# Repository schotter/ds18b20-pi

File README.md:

<div style="font-size: 48pt; color: #e33;">DO NOT USE!</div>

Never produced and it's constructed in a stupid way.
It ignores 1-Wire's bus structure.

<hr/>

# ds18b20-pi

A simple extension board for the raspberry pi 1 model **b** with only **26** GPIO pins.
It's purpose is to make GPIO**4** easily accessible, because it's used for the [1-Wire](https://en.wikipedia.org/wiki/1-Wire) bus.
By easily I mean by using [screw terminal](https://www.reichelt.de/leiterplattenklemme-3-polig-rm-3-5-mm-dg350-3-5-3-p276225.html?&nbc=1)s.
As the [1-Wire](https://en.wikipedia.org/wiki/1-Wire) bus is a **bus**, it makes no sense to create several junctions on the pcb.
Just turn the cable into a [cable harness](https://en.wikipedia.org/wiki/Cable_harness).

That "trick" created space which is now used to switch a floor heating's automatic control electric motor.
Those motors are pretty dumb.
If powered the motor opens the valve, if not it closes the valve.
So there is no communication protocol, just a simple "on/off switch" that can be implemented by a GPIO pin, a relay, a [free-wheeling diode](https://en.wikipedia.org/wiki/Flyback_diode) and a [mosfet](https://en.wikipedia.org/wiki/MOSFET) because the relay needs 5V.
Normally I would add a pull-down resistor (10k) to every mosfet's gate, but there is not enough space.
If things get messy it should be possible to place tht resistors at the bottom side or maybe even just smd resistors between every mosfet's source (square) and gate (middle) pin.

The green leds were added to signal the relay's status and are kind of optional.
As the wires to all sensors got pretty long a [tvs-diode](https://en.wikipedia.org/wiki/Transient-voltage-suppression_diode) was added to prevent damage from esd events.
Unfortunately there is no tht version so I had to pick a smd package.

## bom

| part | description | price | manufacturer | datasheet |
|------|-------------|-------|--------------|-----------|
| [2N 7000 DIO](https://www.reichelt.de/mosfet-n-ch-60v-0-115a-0-4w-to-92-2n-7000-dio-p219075.html) | n-channel mosfet | 0,08 € | [diotec](https://diotec.com/en/productlist.html?productfamily=FET) | [pdf](https://diotec.com/tl_files/diotec/files/pdf/datasheets/2n7000.pdf) |
| [BAT 48 STM](https://www.reichelt.de/schottkydiode-40-v-0-35-a-do-35-bat-48-stm-p219563.html) | schottky diode | 0,04 € | [st](https://www.st.com/en/diodes-and-rectifiers/bat48.html) | [pdf](https://www.st.com/resource/en/datasheet/bat48.pdf) |
| [DG350 3,5-2](https://www.reichelt.de/leiterplattenklemme-2-polig-rm-3-5-mm-dg350-3-5-2-p276224.html) | connector 2-pins | 0,19 € | [degson](http://degson.de/en/pro_detail/id/542) | [pdf](http://degson.de/en/downpdf/id/542.html) |
| [DG350 3,5-3](https://www.reichelt.de/leiterplattenklemme-3-polig-rm-3-5-mm-dg350-3-5-3-p276225.html) | connector 3-pins | 0,28 € | [degson](http://degson.de/en/pro_detail/id/542) | [pdf](http://degson.de/en/downpdf/id/542.html) |
| [HJR-4102-L 5V](https://www.reichelt.de/dil-miniaturrelais-hjr-4102-5v-1-wechsler-5a-hjr-4102-l-5v-p101950.html) | relay | 0,62 € | [tianbo](http://www.tianbo-relay.com/en/products.php?tid=10) | [pdf](http://www.tianbo-relay.com/upload/2019062414532076.pdf) |
| [K-O RD12JN152T52](https://www.reichelt.de/widerstand-kohleschicht-1-5-kohm-0411-500-mw-5-k-o-rd12jn152t52-p237423.html) | 1,5k resistor | 0,08 € | | |
| [LED 3MM 5V GN](https://www.reichelt.de/led-3-mm-bedrahtet-5-v-gruen-20-mcd-60-led-3mm-5v-gn-p54093.html) | green led with embedded resistor | 0,31 € | [kingbright](https://www.kingbright.com/content/listitem/psearch/259) | [pdf](https://cdn-reichelt.de/documents/datenblatt/A500/L-934GD-5V.pdf) |
| [PESD3V3S2UT](https://www.reichelt.de/doppe-esd-schutzdiode-3-3-vrwm-20-vcl-30kv-sot-23-pesd3v3s2ut-p271905.html) | TVS-diode | 0,12 € | [nxp](https://www.nexperia.com/products/esd-protection-tvs-filtering-and-signal-conditioning/automotive-esd-protection-and-tvs/automotive-esd-protection/PESD3V3S2UT.html) | [pdf](https://assets.nexperia.com/documents/data-sheet/PESDXS2UT_SERIES.pdf) |

## schematic

## board

## rendering 

Raspberry Pi 1 GPIO extension board for the 1-wire bus

## note

* `pcb_new`: `File -> Export -> SVG`, *all layers in a single file*, *print board edges*, *color*
* `eeschema`: `File -> Plot`, *SVG*, *Page Size: A4*, *Output mode: color*, *Plot border and title block*

```
$ convert -background white schematic_export.svg schematic_export.png
$ convert -background none board_export.svg board_export.png
```

`convert` is part of [ImageMagick](https://imagemagick.org/index.php).

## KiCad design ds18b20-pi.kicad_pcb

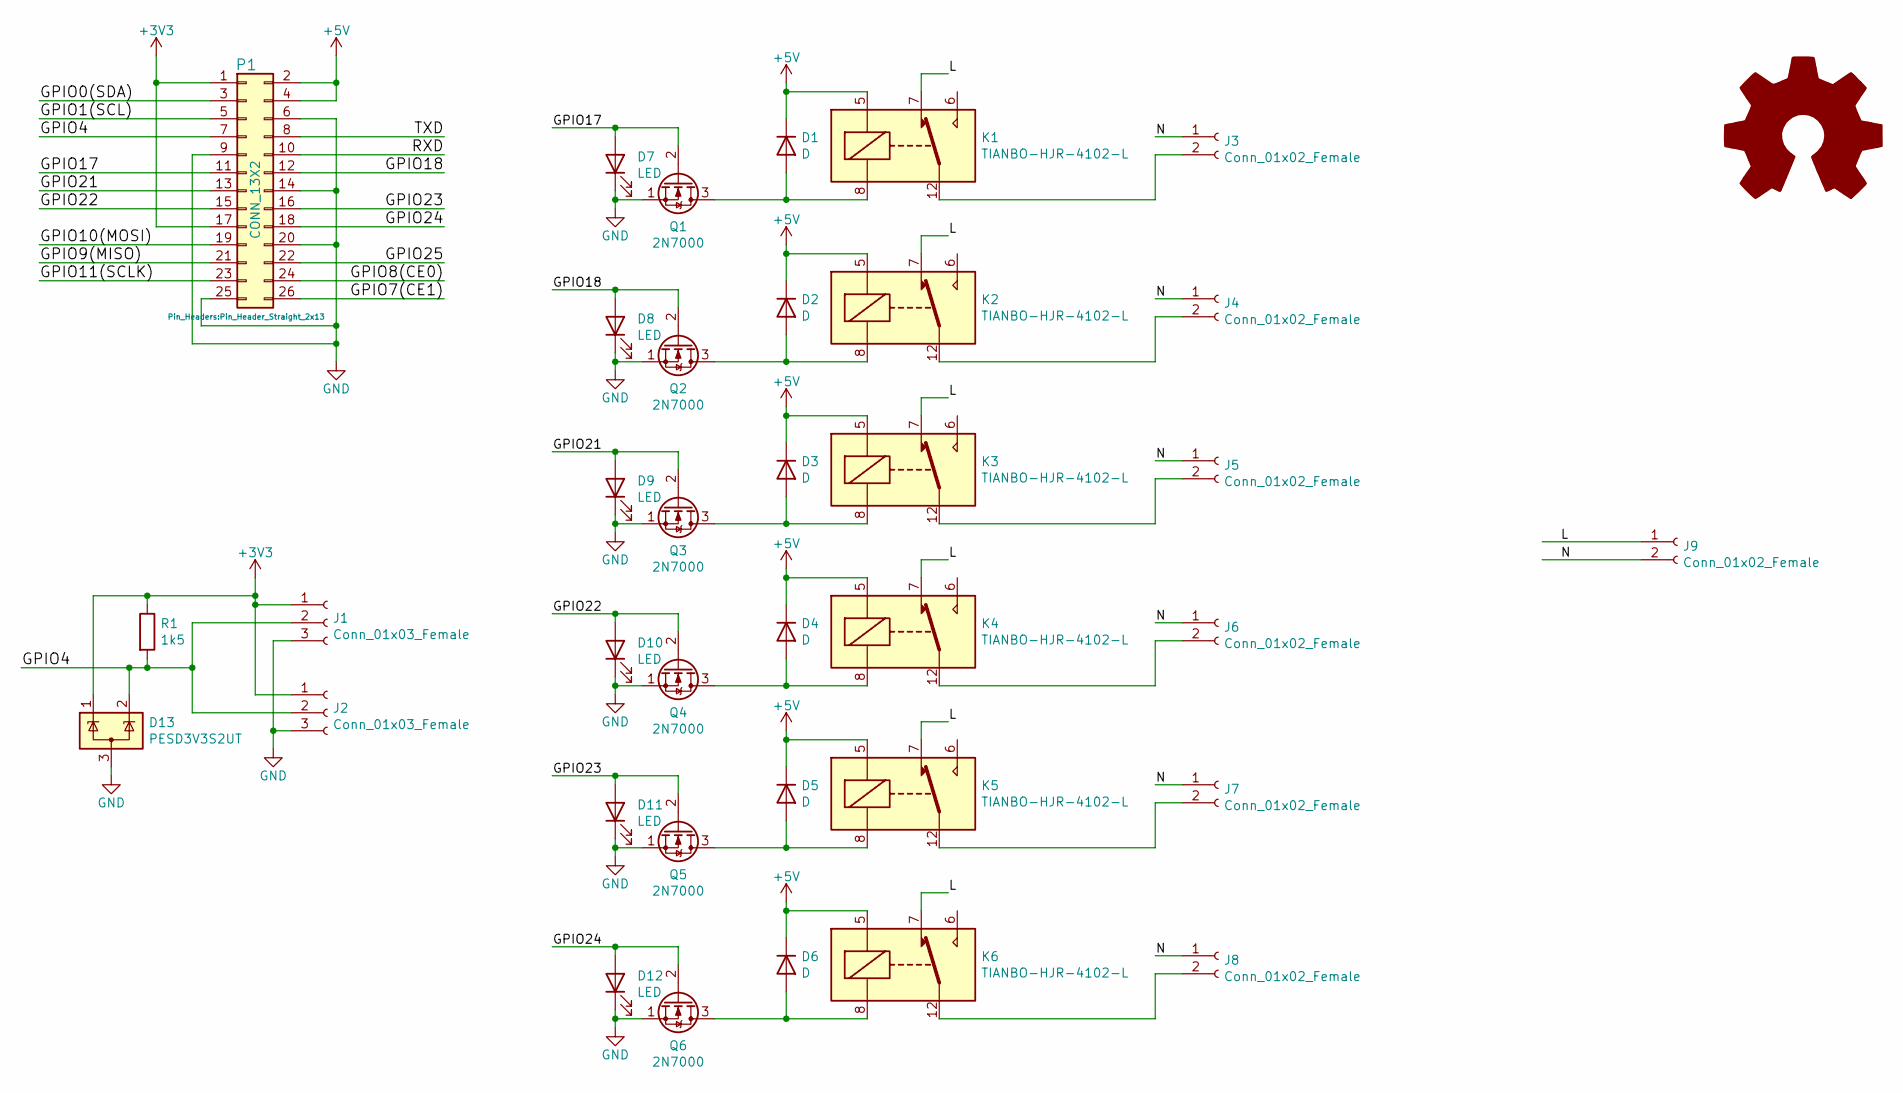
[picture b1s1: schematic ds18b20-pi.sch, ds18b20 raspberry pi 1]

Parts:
D1, D2, D3, D4, D5, D6: D; D_DO-35_SOD27_P7.62mm_Horizontal
D7, D8, D9, D10, D11, D12: LED; LED_D3.0mm
D13: PESD3V3S2UT; SOT-23
J1, J2: Conn_01x03_Female; PhoenixContact_MC_1,5_3-G-3.5_1x03_P3.50mm_Horizontal
J3, J4, J5, J6, J7, J8, J9: Conn_01x02_Female; PhoenixContact_MC_1,5_2-G-3.5_1x02_P3.50mm_Horizontal
K1, K2, K3, K4, K5, K6: TIANBO-HJR-4102-L; Relay_SPDT_HJR-4102
P1: CONN_13X2; Pin_Header_Straight_2x13
Q1, Q2, Q3, Q4, Q5, Q6: 2N7000; TO-92_Inline
R1: 1k5; R_Axial_DIN0411_L9.9mm_D3.6mm_P12.70mm_Horizontal

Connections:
+3V3: D13.1 (K), J1.1, J2.1, P1.1, P1.17, R1.1
+5V: D1.1 (K), D2.1 (K), D3.1 (K), D4.1 (K), D5.1 (K), D6.1 (K), K1.5, K2.5, K3.5, K4.5, K5.5, K6.5, P1.2, P1.4
/GPIO0(SDA): P1.3
/GPIO1(SCL): P1.5
/GPIO4: D13.2 (K), J1.2, J2.2, P1.7, R1.2
/GPIO7(CE1): P1.26
/GPIO8(CE0): P1.24
/GPIO9(MISO): P1.21
/GPIO10(MOSI): P1.19
/GPIO11(SCLK): P1.23
/GPIO17: D7.2 (A), P1.11, Q1.2 (G)
/GPIO18: D8.2 (A), P1.12, Q2.2 (G)
/GPIO21: D9.2 (A), P1.13, Q3.2 (G)
/GPIO22: D10.2 (A), P1.15, Q4.2 (G)
/GPIO23: D11.2 (A), P1.16, Q5.2 (G)
/GPIO24: D12.2 (A), P1.18, Q6.2 (G)
/GPIO25: P1.22
/L: J9.1, K1.7, K2.7, K3.7, K4.7, K5.7, K6.7
/N: J3.1, J4.1, J5.1, J6.1, J7.1, J8.1, J9.2
/RXD: P1.10
/TXD: P1.8
GND: D7.1 (K), D8.1 (K), D9.1 (K), D10.1 (K), D11.1 (K), D12.1 (K), D13.3 (A), J1.3, J2.3, P1.6, P1.9, P1.14, P1.20, P1.25, Q1.1 (S), Q2.1 (S), Q3.1 (S), Q4.1 (S), Q5.1 (S), Q6.1 (S)
unnamed: D1.2 (A), K1.8, Q1.3 (D)
unnamed: D2.2 (A), K2.8, Q2.3 (D)
unnamed: D3.2 (A), K3.8, Q3.3 (D)
unnamed: D4.2 (A), K4.8, Q4.3 (D)
unnamed: D5.2 (A), K5.8, Q5.3 (D)
unnamed: D6.2 (A), K6.8, Q6.3 (D)
unnamed: J3.2, K1.12
unnamed: J4.2, K2.12
unnamed: J5.2, K3.12
unnamed: J6.2, K4.12
unnamed: J7.2, K5.12
unnamed: J8.2, K6.12

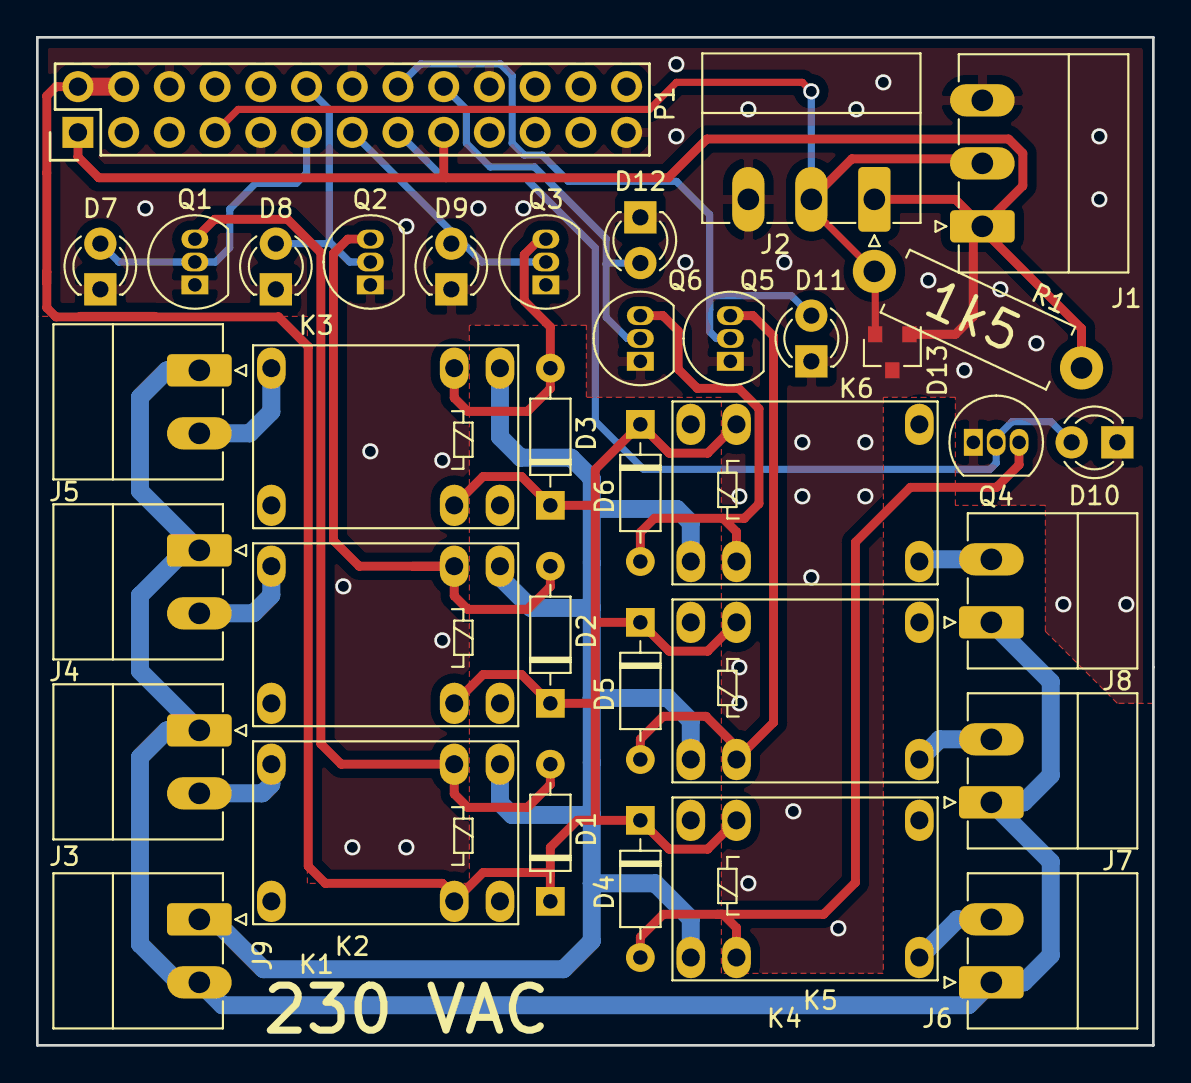
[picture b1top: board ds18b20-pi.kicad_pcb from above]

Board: 2 copper layers, 62.0 x 56.0 mm, 36 parts (0 on the bottom side), 24 nets.

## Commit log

2020-05-29 GPIO4 accessible, 10 slaves combinable
    * DG350 3,5-3: https://www.reichelt.de/leiterplattenklemme-3-polig-rm-3-5-mm-dg350-3-5-3-p276225.html
    The connector used for the rendering is the wrong one, but it has the
    pitch. So it's acceptable.
2020-05-30 Less GPIO4 more relays for motors
2020-05-30 More Vias and more GND
2020-05-30 Typo
2020-05-30 bom: relay
2020-05-30 bom: 1,5k resistor
2020-05-31 bom: manufacturer + datasheet
2020-06-03 Indicator led for each relay
    There are leds that already have a series resistor included to limit the
    current. Those leds are necessary for this board, because there is not
    enough space for addition resistors.
2020-06-03 oshw logo
2020-06-13 tvs diode
    The sensors are connected through long wires, which make it very likely
    for radiation to couple into them and disturb the communication.
    Therefore a tvs diode was added. Unfortunately for a breakdown voltage
    of 3,3V there are only smd packages available.
2020-12-29 Added warning in README
